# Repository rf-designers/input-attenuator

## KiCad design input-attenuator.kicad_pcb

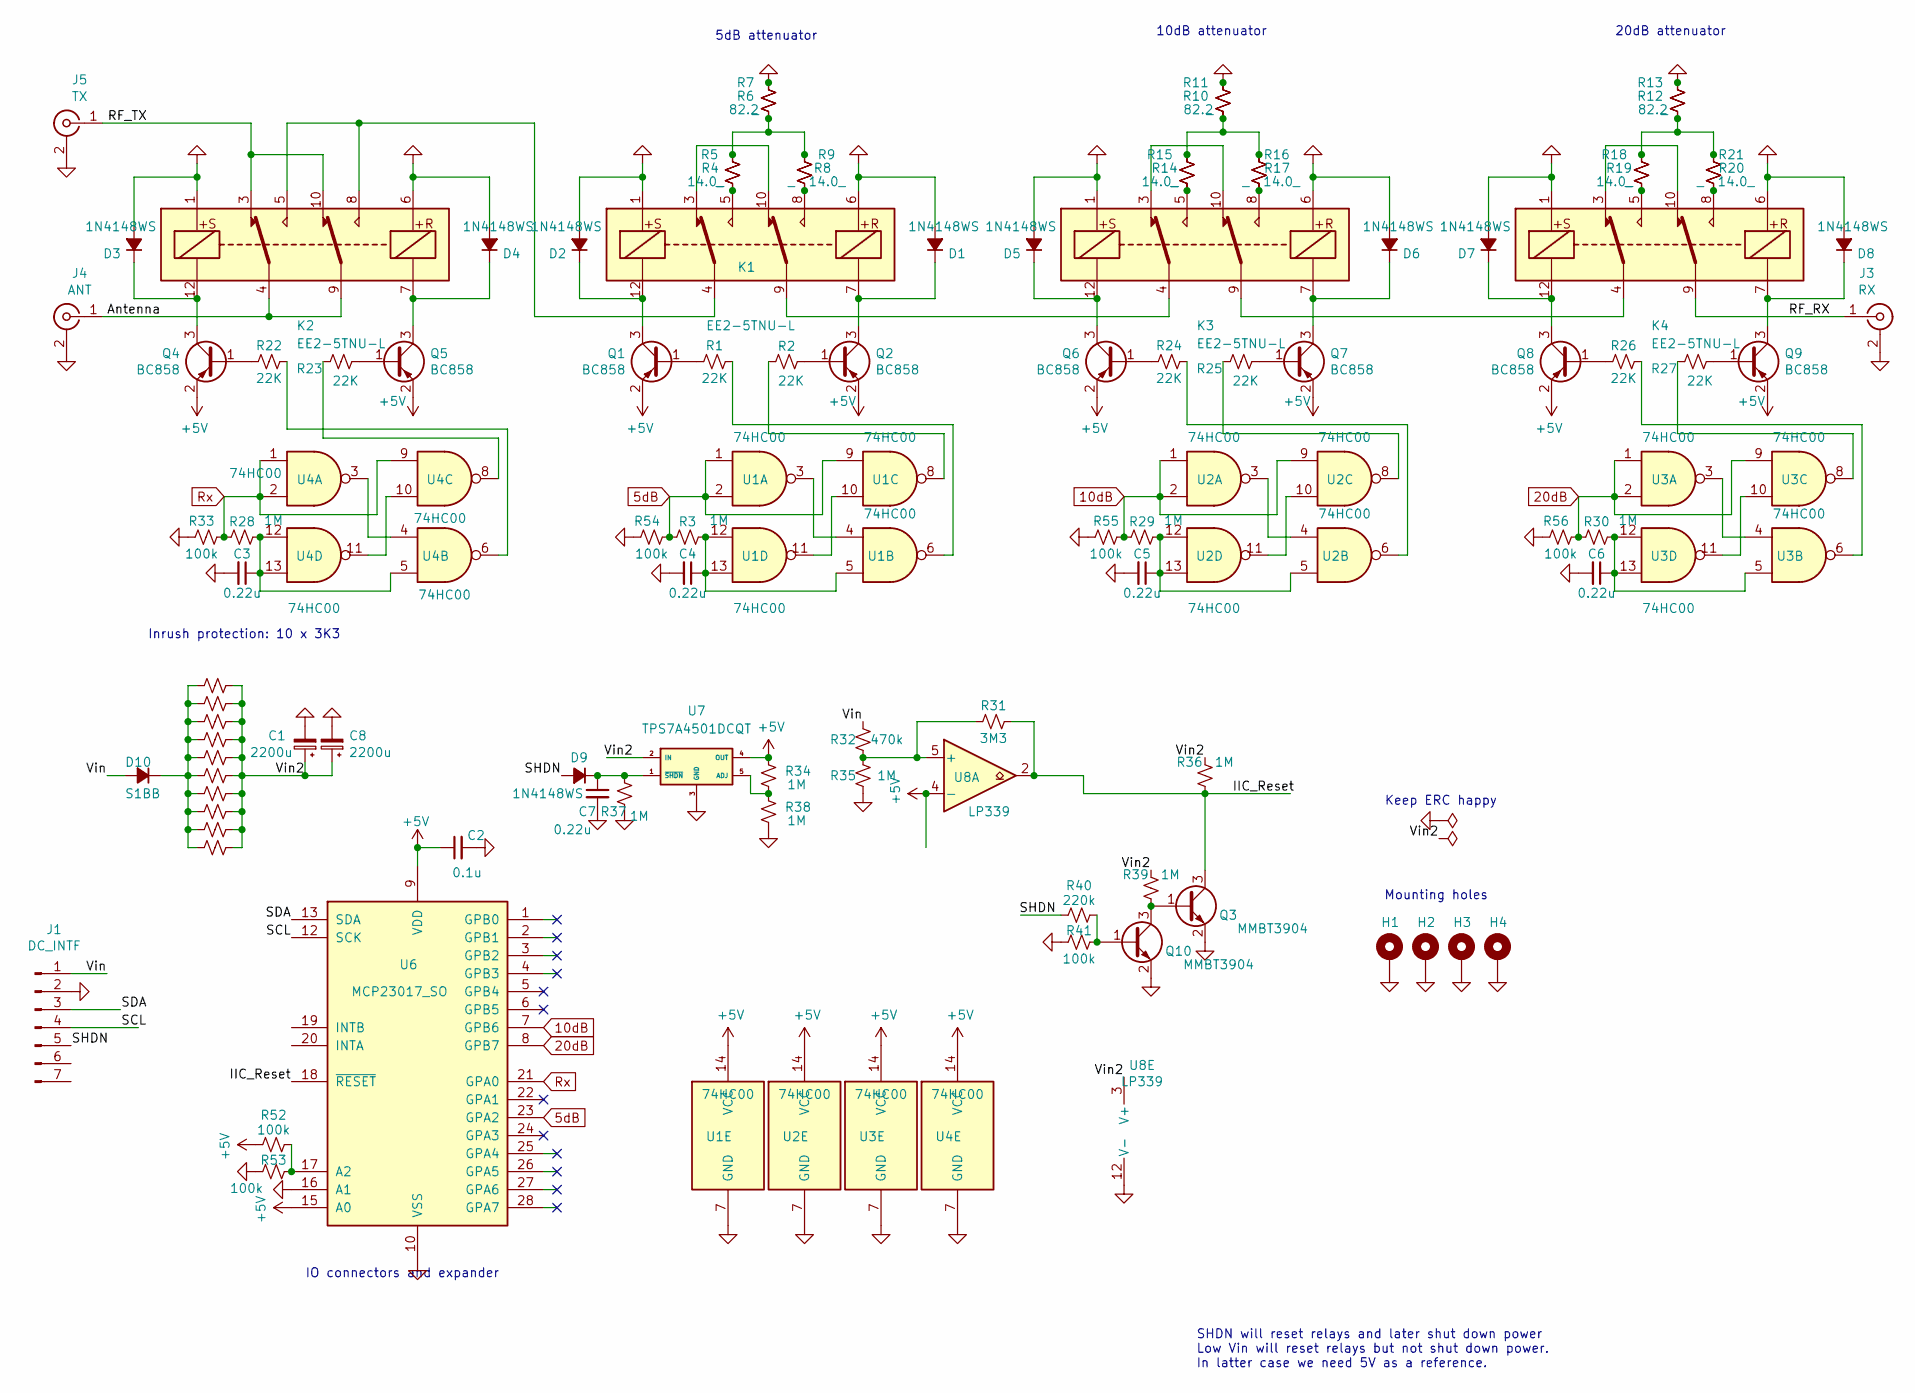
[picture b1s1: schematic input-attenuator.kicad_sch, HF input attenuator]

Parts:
C1, C8: 2200u; CP_Radial_D12.5mm_P7.50mm
C2: 0.1u; C_0805_2012Metric
C3, C4, C5, C6, C7: 0.22u; C_0805_2012Metric
D1, D2, D3, D4, D5, D6, D7, D8, D9: 1N4148WS; D_SOD-323
D10: S1BB; D_SMB_Handsoldering
H1, H2, H3, H4: MountingHole_Pad; MountingHole_3.2mm_M3_ISO7380_Pad
J1: DC_INTF; PinHeader_1x07_P2.54mm_Vertical
J3: RX; SMA_Amphenol_132134_Vertical
J4: ANT; SMA_Amphenol_132134_Vertical
J5: TX; SMA_Amphenol_132134_Vertical
K1, K2, K3, K4: EE2-5TNU-L; Relay_DPDT_Kemet_EE2_NU_DoubleCoil
Q1, Q2, Q4, Q5, Q6, Q7, Q8, Q9: BC858; SOT-23
Q3, Q10: MMBT3904; SOT-23
R1, R2, R22, R23, R24, R25, R26, R27: 22K; R_0805_2012Metric
R3, R28, R29, R30, R34, R35, R36, R37, R38, R39: 1M; R_0805_2012Metric
R4, R8, R14, R17, R19, R20: 14.0_; R_0805_2012Metric
R5, R7, R9, R11, R13, R15, R16, R18, R21: _; R_0805_2012Metric
R6, R10, R12: 82.2; R_0805_2012Metric
R31: 3M3; R_0805_2012Metric
R32: 470k; R_0805_2012Metric
R33, R41, R52, R53, R54, R55, R56: 100k; R_0805_2012Metric
R40: 220k; R_0805_2012Metric
R42, R43, R44, R45, R46, R47, R48, R49, R50, R51: 3K3; R_0805_2012Metric
U1, U2, U3, U4: 74HC00; SO-14_3.9x8.65mm_P1.27mm
U6: MCP23017_SO; SOIC-28W_7.5x17.9mm_P1.27mm
U7: TPS7A4501DCQT; SOT-223-6_TabPin3
U8: LP339; SO-14_3.9x8.65mm_P1.27mm

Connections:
5dB: R3.1, R54.1, U1.1, U1.2, U1.9, U6.23 (GPA2)
10dB: R29.1, R55.1, U2.1, U2.2, U2.9, U6.7 (GPB6)
20dB: R30.1, R56.1, U3.1, U3.2, U3.9, U6.8 (GPB7)
+5V: C2.1, Q1.2 (E), Q2.2 (E), Q4.2 (E), Q5.2 (E), Q6.2 (E), Q7.2 (E), Q8.2 (E), Q9.2 (E), R34.2, R52.2, U1.14 (VCC), U2.14 (VCC), U3.14 (VCC), U4.14 (VCC), U6.9 (VDD), U6.15 (A0), U7.4 (OUT), U8.4 (-)
/Antenna: J4.1 (In), K2.4, K2.9
/IIC_Reset: Q3.3 (C), R31.1, R36.1, U6.18 (~RESET), U8.2
/RF_RX: J3.1 (In), K4.9
/RF_TX: J5.1 (In), K2.3, K2.10
/SCL: J1.4, U6.12 (SCK)
/SDA: J1.3, U6.13 (SDA)
/SHDN: D9.2 (A), J1.5, R40.2
/Vin: D10.2 (A), J1.1, R32.2
/Vin2: C1.1, C8.1, R36.2, R39.2, R42.2, R43.2, R44.2, R45.2, R46.2, R47.2, R48.2, R49.2, R50.2, R51.2, U7.2 (IN), U8.3 (V+)
GND: C1.2, C2.2, C3.2, C4.2, C5.2, C6.2, C7.2, C8.2, D1.2 (A), D2.2 (A), D3.2 (A), D4.2 (A), D5.2 (A), D6.2 (A), D7.2 (A), D8.2 (A), H1.1, H2.1, H3.1, H4.1, J1.2, J3.2 (Ext), J4.2 (Ext), J5.2 (Ext), K1.1, K1.6, K2.1, K2.6, K3.1, K3.6, K4.1, K4.6, Q3.2 (E), Q10.2 (E), R6.2, R7.2, R10.2, R11.2, R12.2, R13.2, R33.2, R35.1, R37.1, R38.1, R41.2, R53.2, R54.2, R55.2, R56.2, U1.7 (GND), U2.7 (GND), U3.7 (GND), U4.7 (GND), U6.10 (VSS), U6.16 (A1), U7.3 (GND), U8.12 (V-)
unnamed: C3.1, R28.2, U4.5, U4.12, U4.13
unnamed: C4.1, R3.2, U1.5, U1.12, U1.13
unnamed: C5.1, R29.2, U2.5, U2.12, U2.13
unnamed: C6.1, R30.2, U3.5, U3.12, U3.13
unnamed: C7.1, D9.1 (K), R37.2, U7.1 (~SHDN)
unnamed: D1.1 (K), K1.7, Q2.3 (C)
unnamed: D2.1 (K), K1.12, Q1.3 (C)
unnamed: D3.1 (K), K2.12, Q4.3 (C)
unnamed: D4.1 (K), K2.7, Q5.3 (C)
unnamed: D5.1 (K), K3.12, Q6.3 (C)
unnamed: D6.1 (K), K3.7, Q7.3 (C)
unnamed: D7.1 (K), K4.12, Q8.3 (C)
unnamed: D8.1 (K), K4.7, Q9.3 (C)
unnamed: D10.1 (K), R42.1, R43.1, R44.1, R45.1, R46.1, R47.1, R48.1, R49.1, R50.1, R51.1
unnamed: K1.4, K2.5, K2.8
unnamed: K1.5, R4.1, R5.1
unnamed: K1.8, R8.2, R9.1
unnamed: K1.9, K3.4
unnamed: K1.3, K1.10
unnamed: K3.5, R14.1, R15.1
unnamed: K3.8, R16.1, R17.2
unnamed: K3.9, K4.4
unnamed: K3.3, K3.10
unnamed: K4.5, R18.1, R19.1
unnamed: K4.8, R20.2, R21.1
unnamed: K4.3, K4.10
unnamed: Q1.1 (B), R1.2
unnamed: Q2.1 (B), R2.2
unnamed: Q4.1 (B), R22.2
unnamed: Q5.1 (B), R23.2
unnamed: Q6.1 (B), R24.2
unnamed: Q7.1 (B), R25.2
unnamed: Q8.1 (B), R26.2
unnamed: Q9.1 (B), R27.2
unnamed: Q10.1 (B), R40.1, R41.1
unnamed: Q3.1 (B), Q10.3 (C), R39.1
unnamed: R4.2, R5.2, R6.1, R7.1, R8.1, R9.2
unnamed: R10.1, R11.1, R14.2, R15.2, R16.2, R17.1
unnamed: R12.1, R13.1, R18.2, R19.2, R20.1, R21.2
unnamed: R23.1, U4.8
unnamed: R24.1, U2.6
unnamed: R25.1, U2.8
unnamed: R31.2, R32.1, R35.2, U8.5 (+)
unnamed: R34.1, R38.2, U7.5 (ADJ)
unnamed: R52.1, R53.1, U6.17 (A2)
unnamed: U1.3, U1.4
unnamed: R1.1, U1.6
unnamed: R2.1, U1.8
unnamed: U1.10, U1.11
unnamed: U2.3, U2.4
unnamed: U2.10, U2.11
unnamed: U3.3, U3.4
unnamed: R26.1, U3.6
unnamed: R27.1, U3.8
unnamed: U3.10, U3.11
unnamed: U4.3, U4.4
unnamed: R22.1, U4.6
unnamed: U4.10, U4.11
Rx: R28.1, R33.1, U4.1, U4.2, U4.9, U6.21 (GPA0)

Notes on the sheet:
IO connectors and expander
Inrush protection: 10 x 3K3
5dB attenuator
10dB attenuator
SHDN will reset relays and later shut down power Low Vin will reset relays but not shut down power. In latter case we need 5V as a reference.
Mounting holes
Keep ERC happy
20dB attenuator

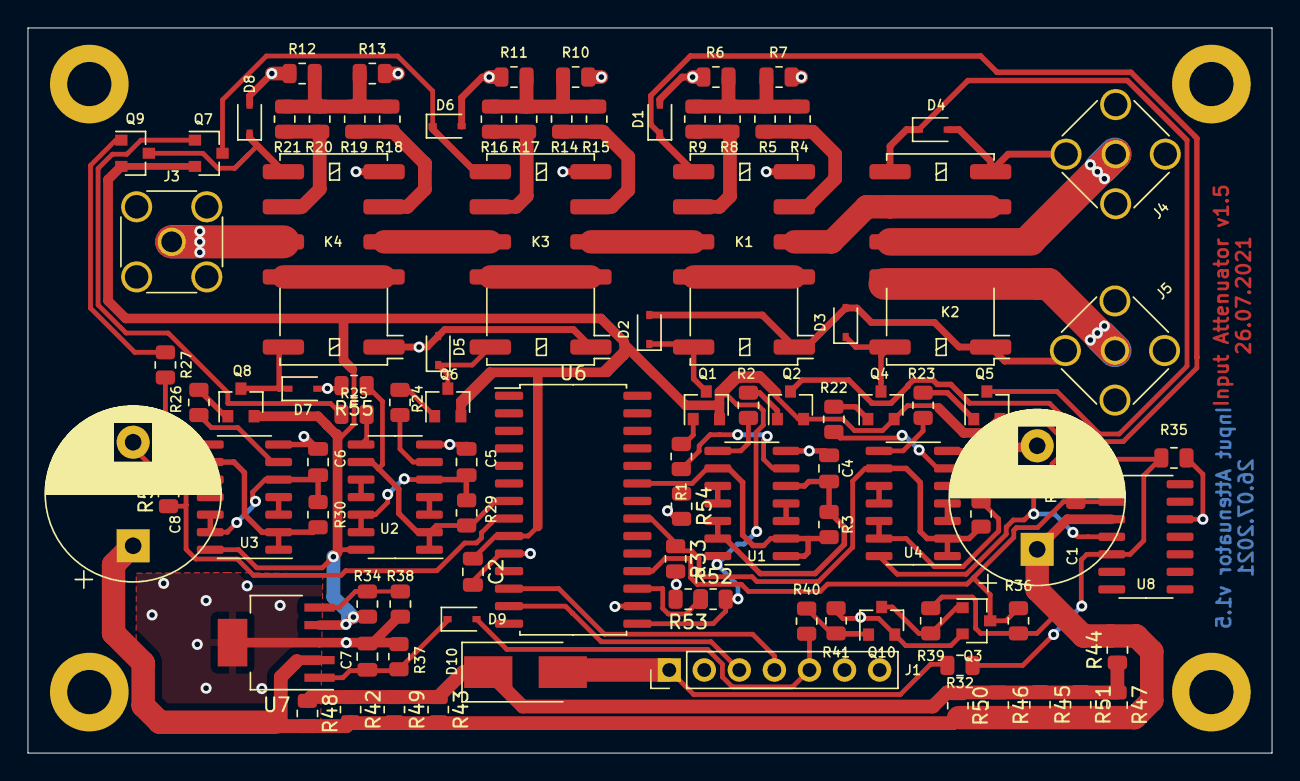
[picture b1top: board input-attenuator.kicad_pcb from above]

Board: 2 copper layers, 90.1 x 52.5 mm, 103 parts (0 on the bottom side), 73 nets.

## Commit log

2021-03-14 Initial import
2021-03-15 noComment
2021-03-15 relays
2021-03-16 relaysPlaced
2021-03-16 Added regulator symbol to custom lib
2021-03-16 addedPowerDown
2021-03-16 Updated input pin header and Vin diode
2021-03-17 lookAtC
2021-03-17 lookAtCx
2021-03-17 final
2021-03-17 moved
2021-03-17 vias
2021-03-17 Added edge cuts, mounting holes and improved silkscreen
2021-03-17 DRC: moved some errors as warning (silkscreen and courtyard) and made small tracks adjustment
2021-03-18 Schema: added inrush resistors, made ERC pass, updated old symbols
2021-03-19 Updated layout with inrush resistor
2021-03-19 Resized board and added auxilliary origin
2021-03-22 Added regulator heat sink tab and module description on FCu
2021-03-22 Layout: added version and date
2021-03-22 Layout: rotated C8
2021-03-22 Layout: moved C8 back into position
2021-07-21 Added an MCP23017
2021-07-26 questionsForYou
